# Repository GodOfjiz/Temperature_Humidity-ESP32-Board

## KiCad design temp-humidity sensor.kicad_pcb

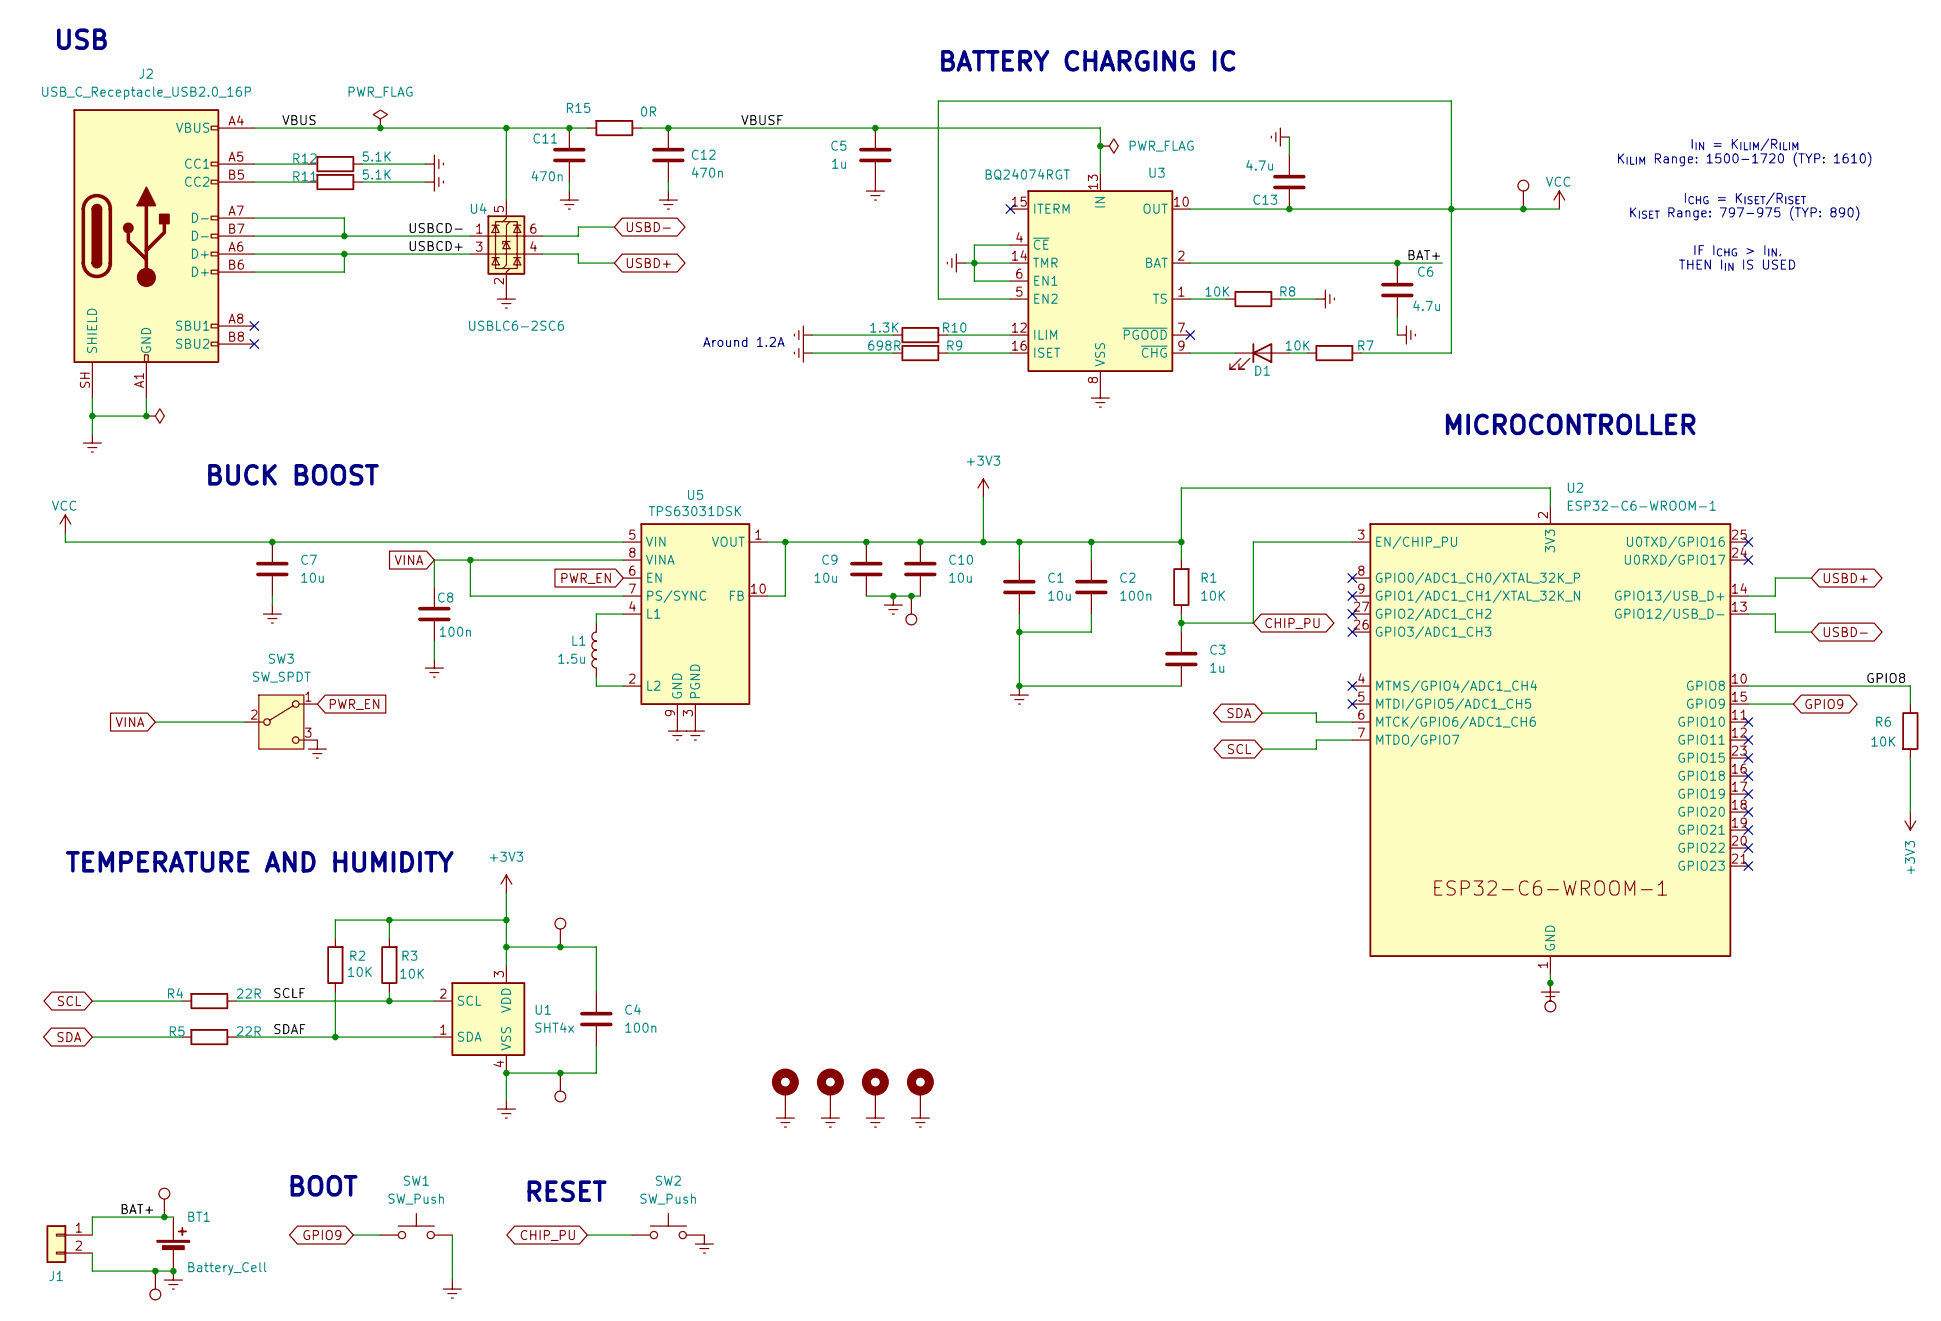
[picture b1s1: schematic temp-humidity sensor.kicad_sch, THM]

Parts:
BT1: Battery_Cell
C1, C7, C9, C10: 10u; C_0805_2012Metric; LCSC C5448891
C2: 100n; C_0805_2012Metric; LCSC C111492
C3: 1u; C_0603_1608Metric; LCSC C106248
C4, C8: 100n; C_0603_1608Metric; LCSC C77055
C5: 1u; C_0805_2012Metric; LCSC C91185
C6, C13: 4.7u; C_0805_2012Metric; LCSC C354262
C11, C12: 470n; C_0603_1608Metric; LCSC C513577
D1: LED; LED_0805_2012Metric; LCSC C19171391
H1, H2, H3, H4: MountingHole; MountingHole_3.2mm_M3_ISO7380_Pad_TopBottom
J1: Conn_01x02; JST_PH_B2B-PH-K_1x02_P2.00mm_Vertical; LCSC Part C131337
J2: USB_C_Receptacle_USB2.0_16P; USB_C_Receptacle_G-Switch_GT-USB-7010ASV; LCSC C2765186
L1: 1.5u; L_Changjiang_FXL0630; LCSC C167217
R1, R2, R3, R6, R7, R8: 10K; R_0603_1608Metric; LCSC C2930027
R4, R5: 22R; R_0603_1608Metric; LCSC C2907129
R9: 698R; R_0603_1608Metric; LCSC C7467401
R10: 1.3K; R_0603_1608Metric; LCSC C2906977
R11, R12: 5.1K; R_0603_1608Metric; LCSC C2907044
R15: 0R; R_0603_1608Metric; LCSC C95177
SW1, SW2: SW_Push; SW_Push_SPST_NO_Alps_SKRK; LCSC C36938886
SW3: SW_SPDT; SW_Slide_SPDT_Straight_CK_OS102011MS2Q
TP2, TP3, TP5, TP6, TP7, TP8, TP9: TestPoint; TestPoint_Pad_D1.0mm
U1: SHT4x; Sensirion_DFN-4_1.5x1.5mm_P0.8mm_SHT4x_NoCentralPad; LCSC C54946589
U2: ESP32-C6-WROOM-1; LCSC C5366877
U3: BQ24074RGT; VQFN-16-1EP_3x3mm_P0.5mm_EP1.6x1.6mm; LCSC C54313
U4: USBLC6-2SC6; SOT-23-6; LCSC C2687116
U5: TPS63031DSK; WSON-10-1EP_2.5x2.5mm_P0.5mm_EP1.2x2mm; LCSC C15516

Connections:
+3V3: C1.1, C2.1, C4.1, C9.1, C10.1, R1.2, R2.2, R3.2, R6.2, TP2.1 (1_1), U1.3 (VDD), U2.2 (3V3), U5.1 (VOUT), U5.10 (FB)
/BAT+: BT1.1 (+), C6.1, J1.1, TP5.1 (1_1), U3.2 (BAT), U3.3 (BAT)
/GPIO8: R6.1, U2.10 (GPIO8)
/SCLF: R3.1, R4.1, U1.2 (SCL)
/SDAF: R2.1, R5.1, U1.1 (SDA)
/USBCD+: J2.A6 (D+), J2.B6 (D+), U4.3 (I/O2)
/USBCD-: J2.A7 (D-), J2.B7 (D-), U4.1 (I/O1)
/VBUS: C11.1, J2.A4 (VBUS), J2.A9 (VBUS), J2.B4 (VBUS), J2.B9 (VBUS), R15.2, U4.5 (VBUS)
/VBUSF: C5.1, C12.1, R15.1, U3.13 (IN)
CHIP_PU: C3.1, R1.1, SW2.1, U2.3 (EN/CHIP_PU)
Earth: BT1.2 (-), C1.2, C2.2, C3.2, C4.2, C5.2, C6.2, C7.2, C8.2, C9.2, C10.2, C11.2, C12.2, C13.2, H1.1 (1_1), H2.1 (1_1), H3.1 (1_1), H4.1 (1_1), J1.2, J2.A1 (GND), J2.A12 (GND), J2.B1 (GND), J2.B12 (GND), J2.SH (SHIELD), R8.2, R9.1, R10.1, R11.1, R12.1, SW1.2, SW2.2, SW3.3 (C), TP6.1 (1_1), TP7.1 (1_1), TP8.1 (1_1), TP9.1 (1_1), U1.4 (VSS), U2.1 (GND), U2.28 (GND), U2.29 (GND), U3.4 (~CE), U3.6 (EN1), U3.8 (VSS), U3.14 (TMR), U3.17 (VSS), U4.2 (GND), U5.3 (PGND), U5.9 (GND), U5.11 (PGND)
GPIO9: SW1.1, U2.15 (GPIO9)
unnamed: D1.2 (A), R7.1
unnamed: D1.1 (K), U3.9 (~CHG)
unnamed: J2.A5 (CC1), R12.2
unnamed: J2.B5 (CC2), R11.2
unnamed: R10.2, U3.12 (ILIM)
unnamed: R9.2, U3.16 (ISET)
unnamed: R8.1, U3.1 (TS)
unnamed: L1.1, U5.4 (L1)
unnamed: L1.2, U5.2 (L2)
PWR_EN: SW3.1 (A), U5.6 (EN)
SCL: R4.2, U2.7 (MTDO/GPIO7)
SDA: R5.2, U2.6 (MTCK/GPIO6/ADC1_CH6)
USBD+: U2.14 (GPIO13/USB_D+), U4.4 (I/O2)
USBD-: U2.13 (GPIO12/USB_D-), U4.6 (I/O1)
VCC: C7.1, C13.1, R7.2, TP3.1 (1_1), U3.5 (EN2), U3.10 (OUT), U3.11 (OUT), U5.5 (VIN)
VINA: C8.1, SW3.2 (B), U5.7 (PS/SYNC), U5.8 (VINA)

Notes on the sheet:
BOOT
BUCK BOOST
RESET
BATTERY CHARGING IC
USB
Around 1.2A
IF I_{CHG} > I_{IN}, THEN I_{IN} IS USED
I_{IN} = K_{ILIM}/R_{ILIM} K_{ILIM} Range: 1500-1720 (TYP: 1610)
I_{CHG} = K_{ISET}/R_{ISET} K_{ISET} Range: 797-975 (TYP: 890)
TEMPERATURE AND HUMIDITY
MICROCONTROLLER

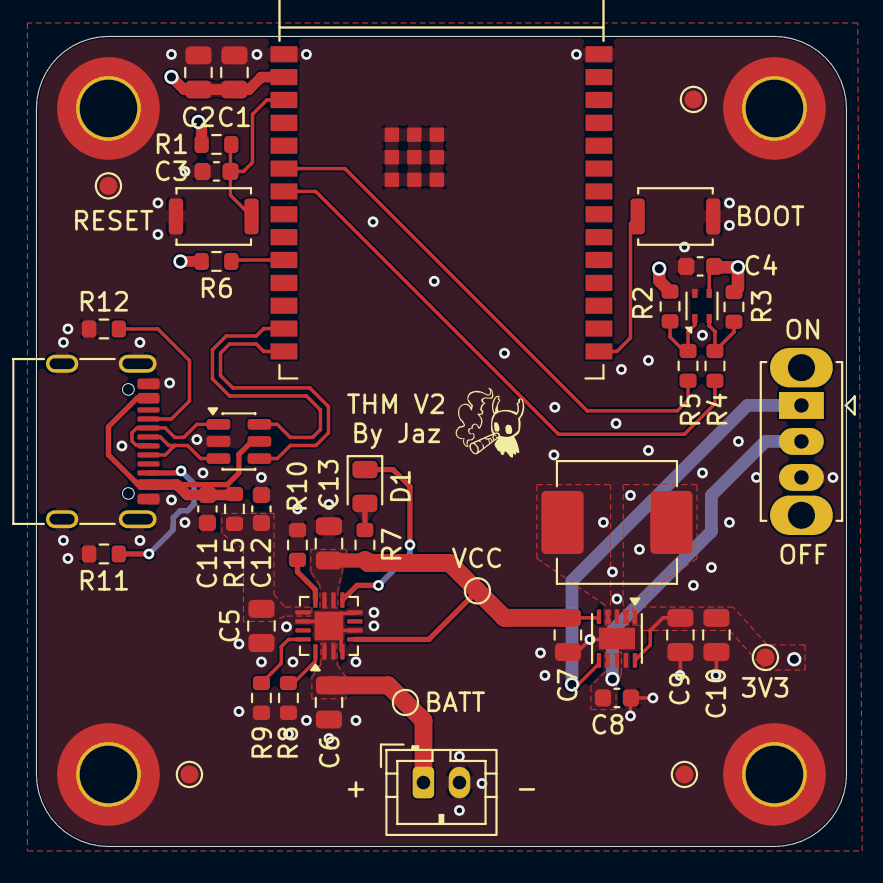
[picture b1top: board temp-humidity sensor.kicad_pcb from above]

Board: 4 copper layers, 45.0 x 45.0 mm, 49 parts (0 on the bottom side), 28 nets.

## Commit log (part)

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2026-05-28 Finished Schematic
2026-06-01 Working On PCB
2026-06-02 Finished Design
2026-06-08 Update to V3
2026-06-10 Udpated to V3.1
